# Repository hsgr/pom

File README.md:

#Popeye on Mars

This project is solving the [Deployable Greenhouse] challenge.

It was developed at [hackerspace.gr] in Athens for [International Space Apps Challenge 2013]

Our solution is a deployable, reusable spinach greenhouse for Mars.
Internally, a fully equipped aeroponic system operates for ~45 days, having all the needed resources, sensors and electronic systems to stabilize the internal environment and help the spinach growth.
Also, there are systems for harvesting produced oxygen during the process and the plants at the end of it.
Externally, photovoltaic panels provide power, while several cover layers protect the system against Mars extreme conditions.

[More details]

[More details]:https://github.com/hsgr/pom/wiki
[Deployable Greenhouse]: http://spaceappschallenge.org/challenge/deployable-greenhouse/
[hackerspace.gr]:http://hackerspace.gr/wiki/Main_Page
[International Space Apps Challenge 2013]:http://spaceappschallenge.org/

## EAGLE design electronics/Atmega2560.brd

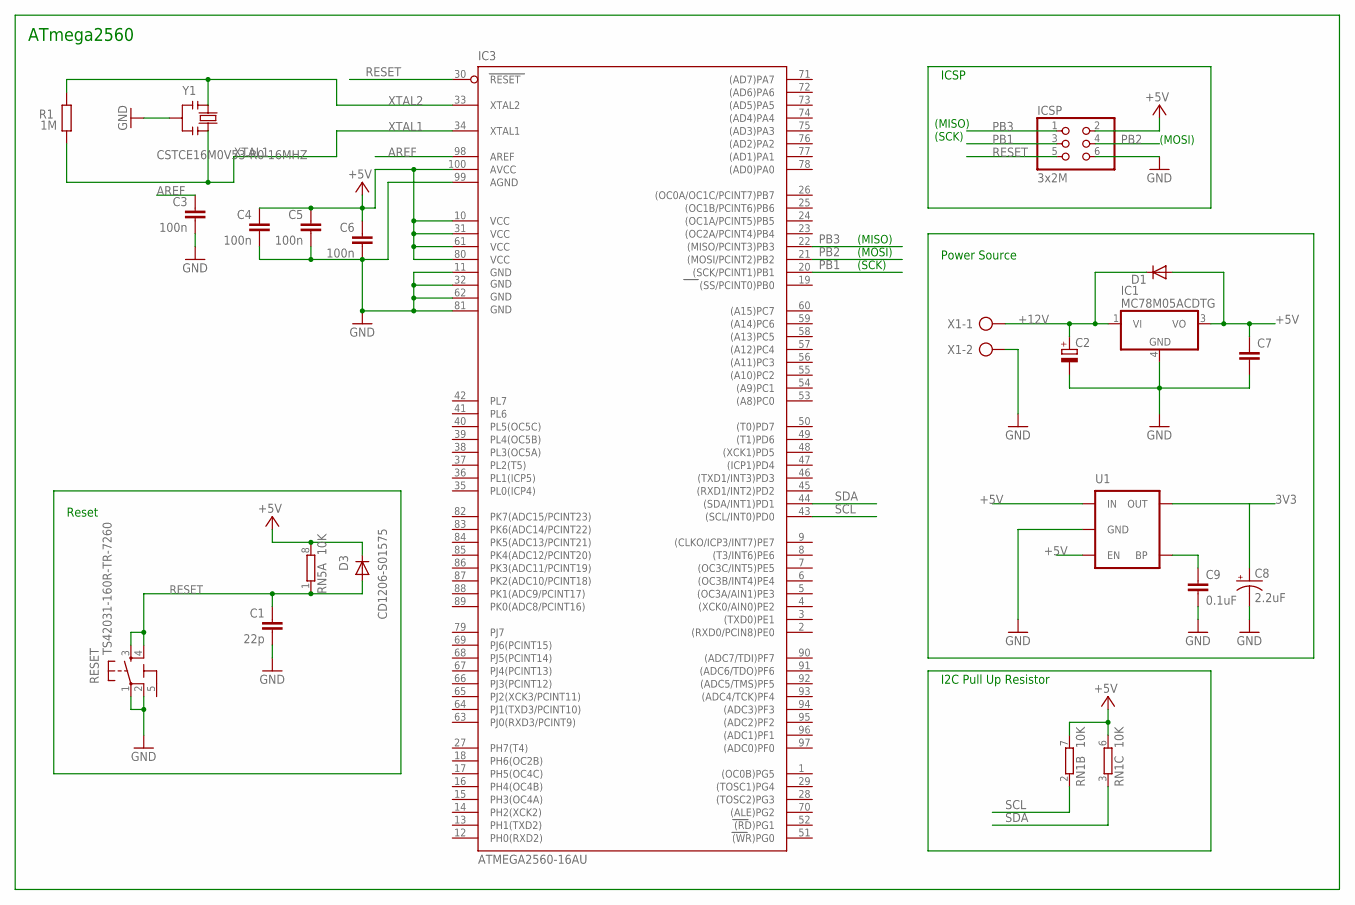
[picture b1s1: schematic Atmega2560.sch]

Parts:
C1: 22p; C0603-ROUND
C2: CPOL-EUE5-13; E5-13
C3, C4, C5, C6: 100n; C0603-ROUND
C7: CAPPTH; CAP-PTH-SMALL
C8: 2.2uF; EIA3216
C9: 0.1uF; 0402-CAP
D1: DIODESMA-KIT; SMA-DIODE-KIT
D3: CD1206-S01575; MINIMELF
IC1: MC78M05ACDTG; DPACK_3
IC3: ATMEGA2560-16AU; TQFP100
ICSP: 3x2M; 2X03
R1: 1M; R0603-ROUND
RESET: TS42031-160R-TR-7260; TS42
RN1, RN5: 10K; CAT16
U1: MIC52053.3V; SOT23-5
X1: AK500/2
Y1: CSTCE16M0V53-R0 16MHZ; RESONATOR

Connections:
3V3: C8.A (+), U1.5 (OUT)
5-GND: RESET.5 (5-GND)
+5V: C4.1, C5.1, C6.1, C7.1, D1.A, D3.C, IC1.3 (VO), IC3.10 (VCC), IC3.31 (VCC1), IC3.61 (VCC2), IC3.80 (VCC3), IC3.100 (AVCC), ICSP.2, RN1.6 (2), RN1.7 (2), RN5.8 (2), U1.1 (IN), U1.3 (EN)
+12V: C2.+, D1.C, IC1.1 (VI), X1.1
AREF: C3.1, IC3.98 (AREF)
GND: C1.2, C2.-, C3.2, C4.2, C5.2, C6.2, C7.2, C8.C (-), C9.2, IC1.4 (GND), IC3.11 (GND), IC3.32 (GND1), IC3.62 (GND2), IC3.81 (GND3), IC3.99 (AGND), ICSP.6, RESET.1, RESET.2, U1.2 (GND), X1.2, Y1.2
unnamed: C9.1, U1.4 (BP)
PB1: IC3.20 ((SCK/PCINT1)PB1), ICSP.3
PB2: IC3.21 ((MOSI/PCINT2)PB2), ICSP.4
PB3: IC3.22 ((MISO/PCINT3)PB3), ICSP.1
RESET: C1.1, D3.A, IC3.30 (RESET), ICSP.5, RESET.3, RESET.4, RN5.1
SCL: IC3.43 ((SCL/INT0)PD0), RN1.2 (1)
SDA: IC3.44 ((SDA/INT1)PD1), RN1.3 (1)
XTAL1: IC3.34 (XTAL1), R1.1, Y1.3
XTAL2: IC3.33 (XTAL2), R1.2, Y1.1

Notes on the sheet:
(MOSI)
(MISO)
(SCK)
ICSP
I2C Pull Up Resistor
Reset
Power Source
ATmega2560

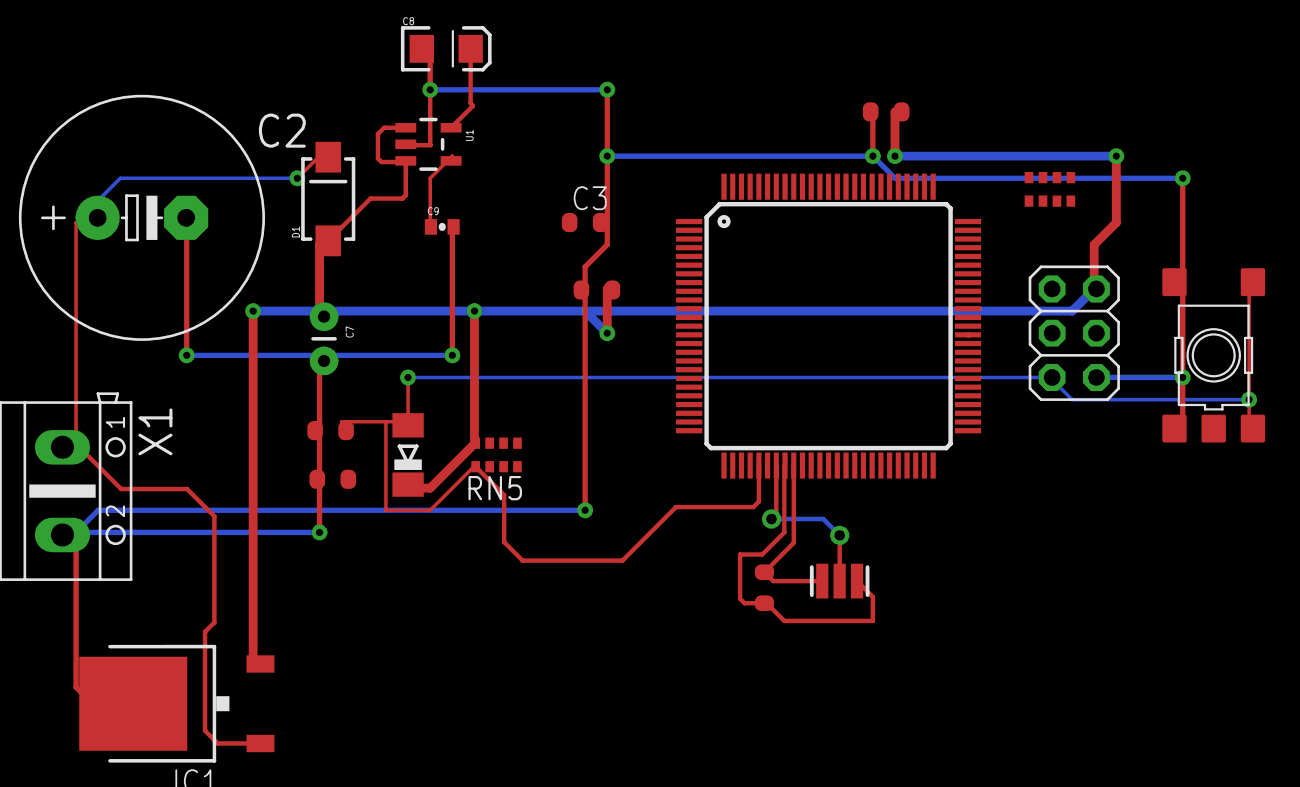
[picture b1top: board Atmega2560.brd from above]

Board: 2 copper layers, 21 parts (0 on the bottom side), 14 nets.

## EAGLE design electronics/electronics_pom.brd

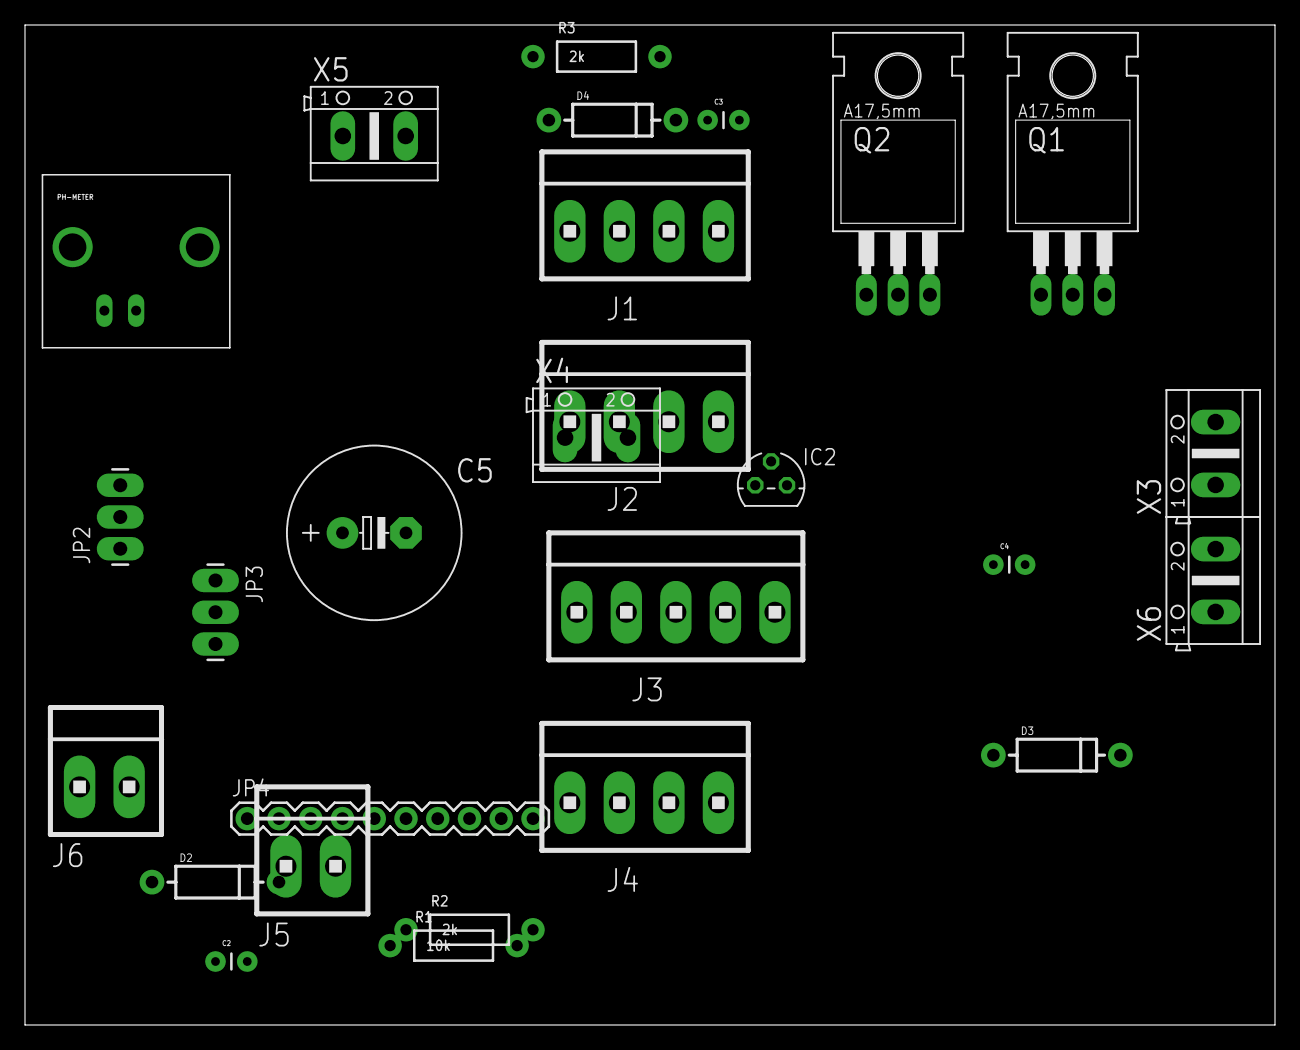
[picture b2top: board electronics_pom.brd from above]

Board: 2 copper layers, 100.0 x 80.0 mm, 27 parts (0 on the bottom side), 13 nets, no tracks yet.

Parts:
C2, C3, C4: 0.1u; CAP-PTH-SMALL
C5: 2200u; E5-13
D2, D3, D4: DIODE-1N4001
IC2: 78L05Z; TO92
J1, J2, J4: 1X4MTA
J3: 1X5MTA
J5, J6: 1X2MTA
JP2, JP3: 1X03_LONGPADS
JP4: M10"; 1X10
PH-METER: BNCPTH; BNC
Q1, Q2: IRLZ44Z; TO220BH
R1: 10k; AXIAL-0.4
R2, R3: 2k; AXIAL-0.4
X3, X4, X5, X6: AK500/2

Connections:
3V3: J2.1, J3.1, J3.5, J4.2, JP4.1
12V: C2.2, C3.2, C5.+, D2.C, D3.C, D4.C, IC2.3, J6.2, X3.2, X5.1, X6.2
GND: C4.1, C5.-, IC2.2, J1.1, J2.2, J3.2, J4.1, J5.1, J6.1, JP2.3, JP3.3, JP4.2, PH-METER.GND, Q1.S, Q2.S, R2.P$1, R3.P$1, X4.1, X5.2
IO36: J5.2, R1.P$2
M_D: C3.1, Q2.D, X6.1
M_PN: C2.1, D2.A, Q1.D, X3.1
PRB: JP3.2, PH-METER.S
PWM4: Q2.G, R3.P$2
PWM9: Q1.G, R2.P$2
S$1: J1.2, R1.P$1
SCL: J1.3, J2.3, J3.3, J4.3, JP4.5
SDA: J1.4, J2.4, J3.4, J4.4, JP4.6
VIN_UC: C4.2, D3.A, IC2.1, X4.2

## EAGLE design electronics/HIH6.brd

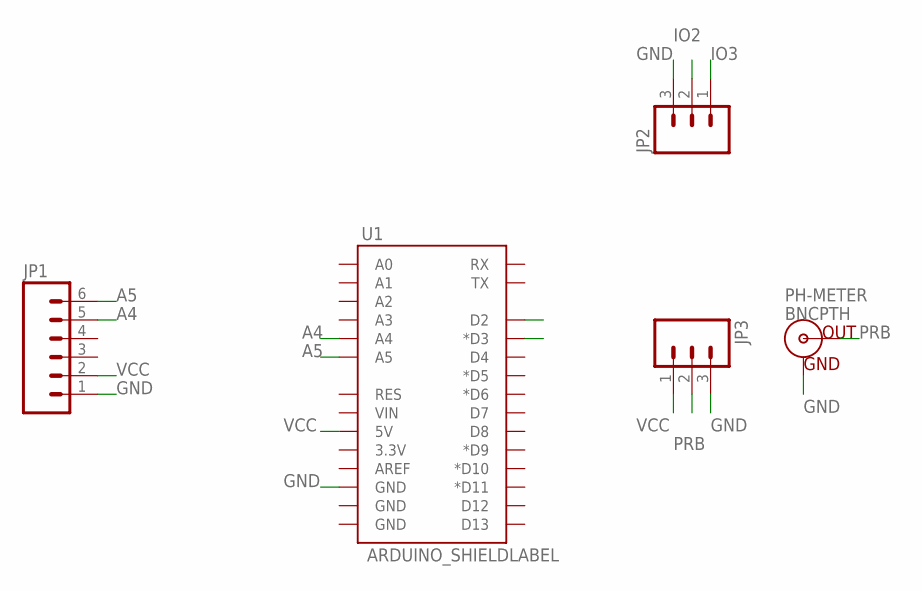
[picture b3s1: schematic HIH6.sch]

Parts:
JP1: M06LONGPADS; 1X06_LONGPADS
JP2, JP3: M03LONGPADS; 1X03_LONGPADS
PH-METER: BNCPTH; BNC
U1: ARDUINO_SHIELDLABEL; DUEMILANOVE_SHIELD

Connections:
A4: JP1.5, U1.A4
A5: JP1.6, U1.A5
GND: JP1.1, JP2.3, JP3.3, PH-METER.GND, U1.GND@2 (GND)
IO2: JP2.2, U1.D2
IO3: JP2.1, U1.D3 (*D3)
PRB: JP3.2, PH-METER.S (OUT)
VCC: JP1.2, JP3.1, U1.5V

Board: 2 copper layers, 5 parts (0 on the bottom side), 7 nets, no tracks yet.

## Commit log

2013-04-20 First document of greenhouse(50% ready)
2013-04-20 second update of the project
2013-04-20 those are the last changes
2013-04-20 arduino code for automatation
2013-04-21 More files came in with code and boards
2013-04-21 deleted emply folders
2013-04-21 deleted empty files
2013-04-21 latest 3D update of mars greenhouse
2013-04-21 updated code with pressure automation
2013-04-21 latest update of 3d model
2013-04-21 updated code for oxygen control
2013-04-21 final model
2013-04-21 last update with new panels and new sensor
2013-04-21 arduino board code update
2013-04-21 This is a simple schematic for pom electronics.
2013-04-21 photos of our project
2013-04-21 Document about the way this farm is working
2013-04-21 Amended electronics documentation
2013-04-23 Documentation update
2013-04-30 three old electronic files deleted
2013-04-30 arduino code update
2013-04-30 electronics diagrams
2013-04-30 updated electronics files
2013-04-30 electronics new files
2013-04-30 an arduino file who left behind
2013-04-30 last update if blender 3d model file
2013-05-01 new photos from inside

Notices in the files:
parts and their libraries:
SparkFun-Capacitors: Licensing: CC v3.0 Share-Alike You are welcome to use this library for commercial purposes.
